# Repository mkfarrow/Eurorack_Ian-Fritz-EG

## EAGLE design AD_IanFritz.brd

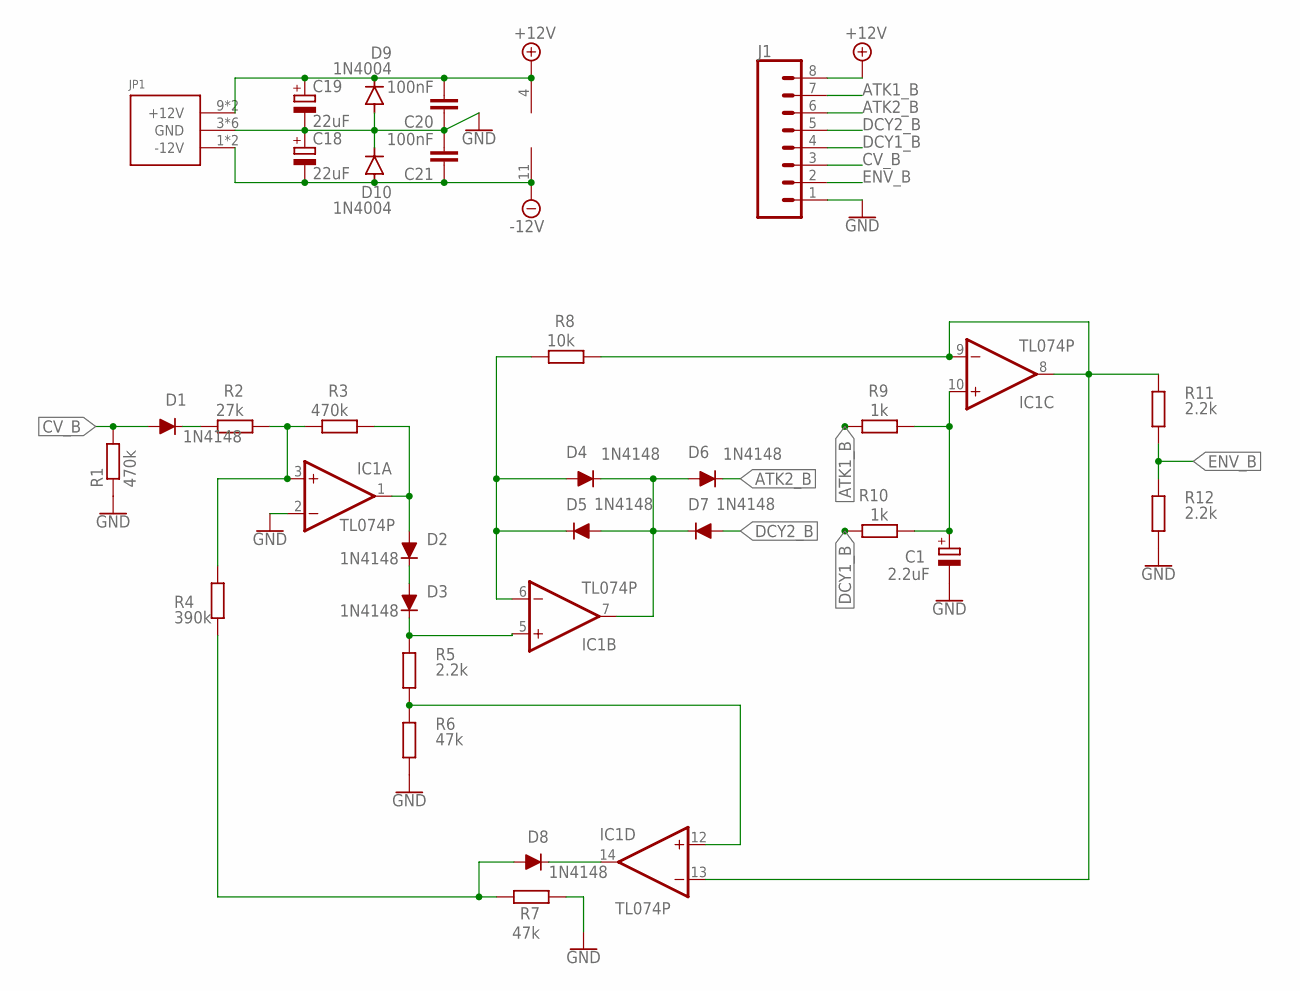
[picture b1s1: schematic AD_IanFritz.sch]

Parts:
C1: 2.2uF; E2-4
C18, C19: 22uF; E2-4
C20, C21: 100nF; C2.5-3
D1, D2, D3, D4, D5, D6, D7, D8: 1N4148; DO-35
D9, D10: 1N4004; DO41-10
IC1: TL074P; DIL14
J1: CONN_08"; 1X08
JP1: POWER_SIMPLE10; POWER_10
R1, R3: 470k; 7MM_RESISTOR
R2: 27k; 7MM_RESISTOR
R4: 390k; 7MM_RESISTOR
R5, R11, R12: 2.2k; 7MM_RESISTOR
R6, R7: 47k; 7MM_RESISTOR
R8: 10k; 7MM_RESISTOR
R9, R10: 1k; 7MM_RESISTOR

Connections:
+12V: C19.+, C20.2, D9.C, IC1.4 (V+), J1.8, JP1.9 (+12V), JP1.10 (+12V)
-12V: C18.-, C21.1, D10.A, IC1.11 (V-), JP1.1 (-12V), JP1.2 (-12V)
ATK1_B: J1.7, R9.2
ATK2_B: D6.C, J1.6
CV_B: D1.A, J1.3, R1.2
DCY1_B: J1.4, R10.2
DCY2_B: D7.A, J1.5
ENV_B: J1.2, R11.2, R12.1
GND: C1.-, C18.+, C19.-, C20.1, C21.2, D9.A, D10.C, IC1.2 (-IN), J1.1, JP1.3 (GND), JP1.4 (GND), JP1.5 (GND), JP1.6 (GND), JP1.7 (GND), JP1.8 (GND), R1.1, R6.1, R7.1, R12.2
unnamed: D3.C, IC1.5 (+IN), R5.1
unnamed: D1.C, R2.2
unnamed: IC1.3 (+IN), R2.1, R3.2, R4.1
unnamed: D2.A, IC1.1 (OUT), R3.1
unnamed: D2.C, D3.A
unnamed: IC1.12 (+IN), R5.2, R6.2
unnamed: D4.A, D5.C, IC1.6 (-IN), R8.2
unnamed: D4.C, D5.A, D6.A, D7.C, IC1.7 (OUT)
unnamed: D8.A, R4.2, R7.2
unnamed: D8.C, IC1.14 (OUT)
unnamed: IC1.8 (OUT), IC1.9 (-IN), IC1.13 (-IN), R8.1, R11.1
unnamed: C1.+, IC1.10 (+IN), R9.1, R10.1

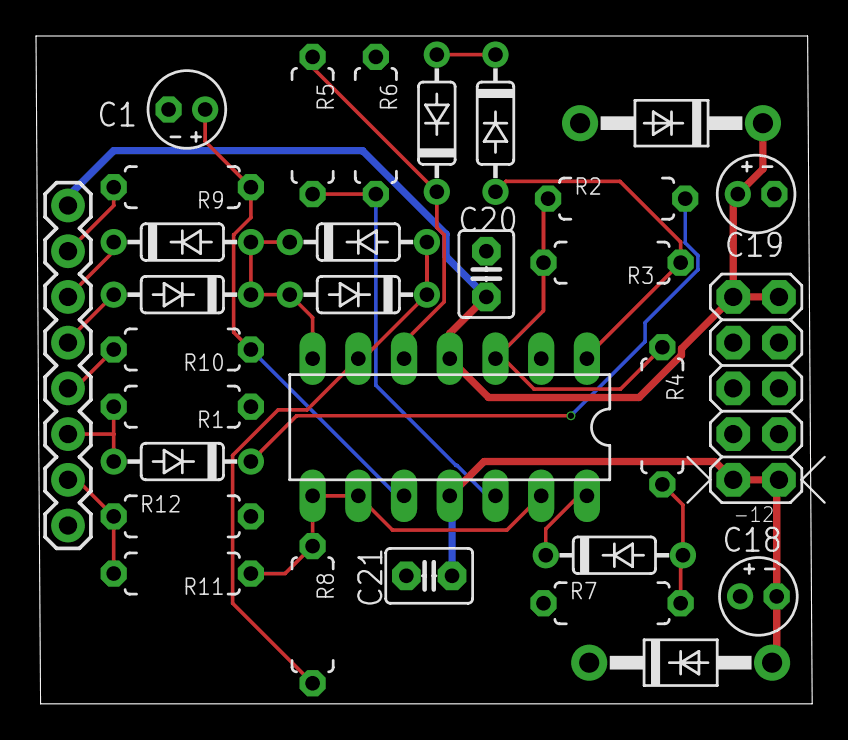
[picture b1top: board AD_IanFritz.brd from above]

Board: 2 copper layers, 43.1 x 37.1 mm, 30 parts (0 on the bottom side), 21 nets.

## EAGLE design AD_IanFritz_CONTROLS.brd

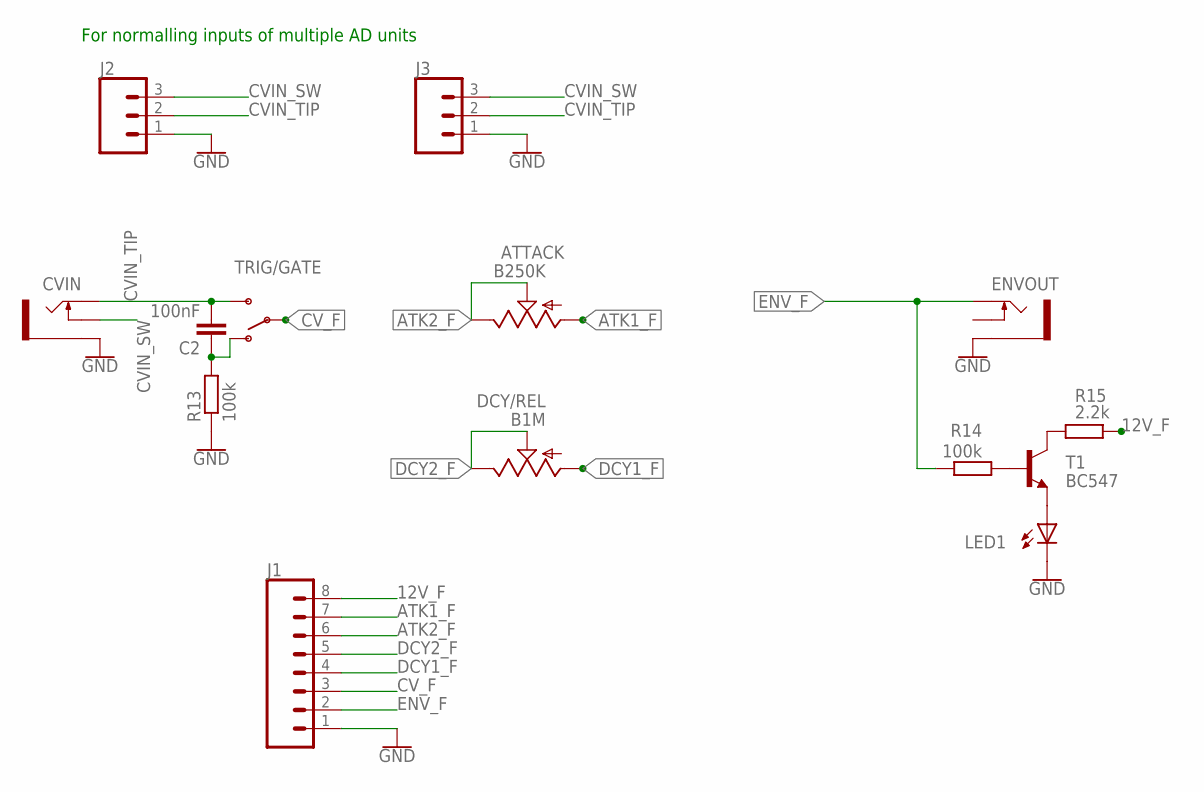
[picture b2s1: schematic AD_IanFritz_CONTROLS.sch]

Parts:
ATTACK: B250K; 9MM_SNAP-IN_POT
C2: 100nF; C2.5-3
CVIN: THONKICONNNEW; WQP-PJ301M-12_JACK
DCY/REL: B1M; 9MM_SNAP-IN_POT
ENVOUT: THONKICONNNEW; WQP-PJ301M-12_JACK
J1: CONN_08"; 1X08
J2, J3: CONN_031X03_NO_SILK; 1X03_NO_SILK
LED1: LED3MM
R13, R14: 100k; 7MM_RESISTOR
R15: 2.2k; 7MM_RESISTOR
T1: BC547; TO92
TRIG/GATE: SUBMINI_SPDT; SUBMINI_TOGGLE

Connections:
12V_F: J1.8, R15.1
ATK1_F: ATTACK.1 (A), J1.7
ATK2_F: ATTACK.2 (S), ATTACK.3 (E), J1.6
CVIN_SW: CVIN.P$2_SWITCH (SWITCH), J2.3, J3.3
CVIN_TIP: C2.2, CVIN.P$1_TIP (TIP), J2.2, J3.2, TRIG/GATE.3 (S)
CV_F: J1.3, TRIG/GATE.COM (COMMON)
DCY1_F: DCY/REL.1 (A), J1.4
DCY2_F: DCY/REL.2 (S), DCY/REL.3 (E), J1.5
ENV_F: ENVOUT.P$1_TIP (TIP), J1.2, R14.2
GND: CVIN.P$3_SLEEVE (SLEEVE), ENVOUT.P$3_SLEEVE (SLEEVE), J1.1, J2.1, J3.1, LED1.K (C), R13.1
unnamed: C2.1, R13.2, TRIG/GATE.1 (O)
unnamed: LED1.A, T1.1 (E)
unnamed: R14.1, T1.2 (B)
unnamed: R15.2, T1.3 (C)

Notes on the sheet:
For normalling inputs of multiple AD units

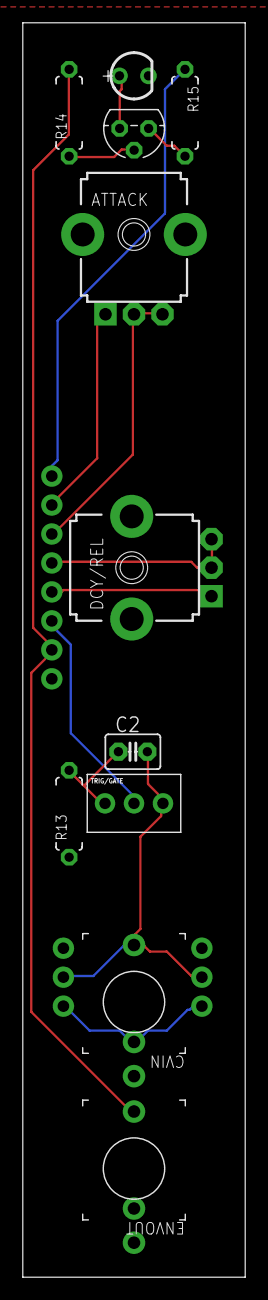
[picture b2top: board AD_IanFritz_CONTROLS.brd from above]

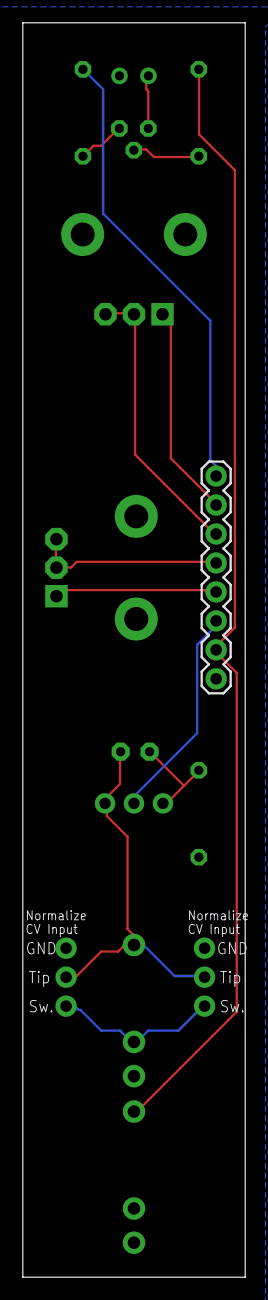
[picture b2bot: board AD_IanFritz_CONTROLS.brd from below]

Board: 2 copper layers, 19.5 x 110.0 mm, 14 parts (3 on the bottom side), 14 nets.

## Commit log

2022-12-21 uploaded eagle files
2022-12-21 remove unnecessary file
2022-12-22 adding images

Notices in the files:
parts and their libraries:
SparkFun-Connectors: Licensing: Creative Commons ShareAlike 4.0 International - https://creativecommons.org/licenses/by-sa/4.0
